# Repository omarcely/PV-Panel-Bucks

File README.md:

# PV-Panel-Bucks
Proyecto de electrónica de potencia

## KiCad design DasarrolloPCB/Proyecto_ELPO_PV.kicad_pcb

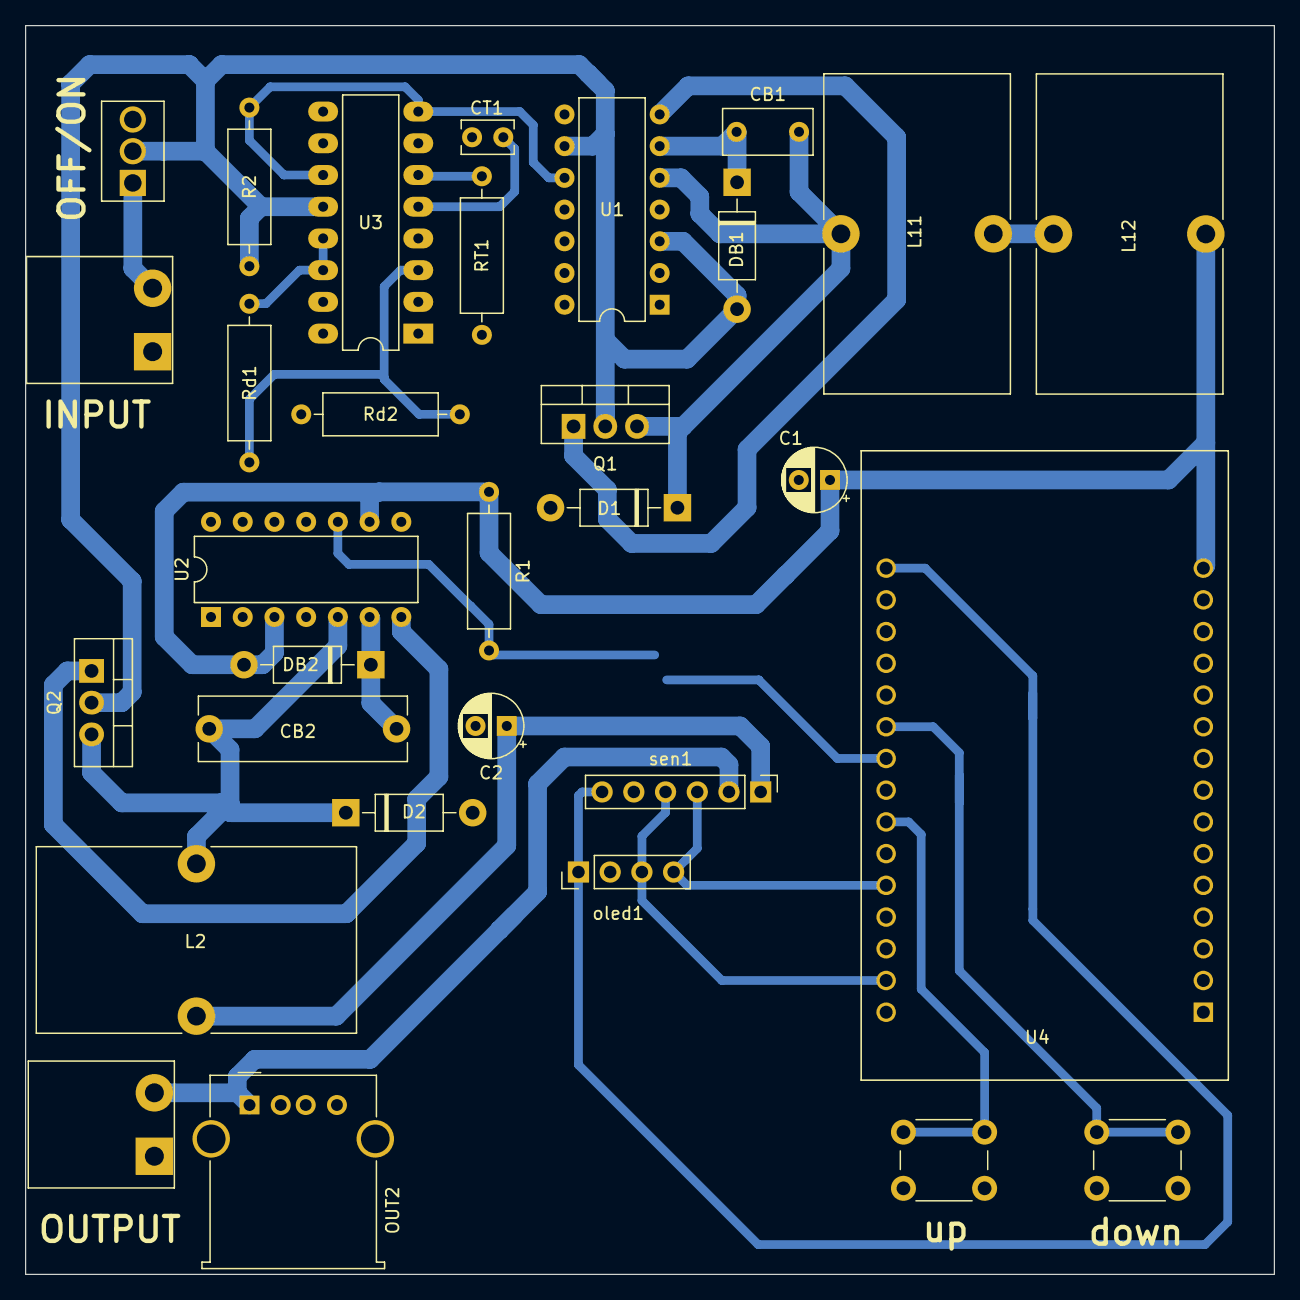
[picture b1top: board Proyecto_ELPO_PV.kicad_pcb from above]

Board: 2 copper layers, 100.0 x 100.0 mm, 32 parts (1 on the bottom side), 25 nets.

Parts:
C1: 10uf; CP_Radial_D5.0mm_P2.50mm
C2: 2.7uF; CP_Radial_D5.0mm_P2.50mm
CB1: 12n; C_Rect_L7.0mm_W3.5mm_P5.00mm
CB2: 0.47uF; C_Rect_L16.5mm_W5.0mm_P15.00mm_MKT
CT1: 5nF; C_Rect_L4.0mm_W2.5mm_P2.50mm
D1, D2: UF4005; D_DO-41_SOD81_P10.16mm_Horizontal
DB1, DB2: UF4005; D_DO-41_SOD81_P10.16mm_Horizontal
INPUT: Solar_Cell; TerminalBlock_bornier-2_P5.08mm
L2, L11, L12: 1mH; L_Toroid_Vertical_L25.4mm_W14.7mm_P12.20mm_Vishay_TJ5_BigPa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
OFF/ON: SW; PinHeader_1x02_P2.54mm_Horizontal
OUT2: USB_A; USB_A_Molex_67643_Horizontal
OUTPUT: bornera; TerminalBlock_bornier-2_P5.08mm
Q1, Q2: IRFZ44N; TO-220-3_Vertical
Q3: 2N7002; SOT-23
R1: 10k; R_Axial_DIN0309_L9.0mm_D3.2mm_P12.70mm_Horizontal
R2: 2.2k; R_Axial_DIN0309_L9.0mm_D3.2mm_P12.70mm_Horizontal
RT1: 2.2k; R_Axial_DIN0309_L9.0mm_D3.2mm_P12.70mm_Horizontal
Rd1: 150k; R_Axial_DIN0309_L9.0mm_D3.2mm_P12.70mm_Horizontal
Rd2: 120k; R_Axial_DIN0309_L9.0mm_D3.2mm_P12.70mm_Horizontal
U1, U2: IR2110; DIP-14_W7.62mm
U3: TL494; DIP-16_W7.62mm_LongPads
U4: ESP32-DEVKITC-32D; MODULE_ESP32-DEVKITC-32D
down: btn; SW_PUSH_6mm
oled1: 1.3'' 128x64; PinHeader_1x04_P2.54mm_Vertical
sen1: 1NA219; PinHeader_1x06_P2.54mm_Vertical
up: btn; SW_PUSH_6mm

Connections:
/TL494/PWM: R2.2, U1.10, U3.8, U3.11
/buck1/Vs: CB1.2, D1.1, L11.1, Q1.3, U1.5
/buck2/Vout: C2.1, L2.2, sen1.6
/buck2/Vs: CB2.2, D2.1, L2.1, Q2.3, U2.5
/driver1/PWM_out: Q1.1, U1.7
/driver2/PWM_in: Q3.3, R1.2, U2.10
/driver2/PWM_out: Q2.1, U2.7
/driver2/Vcc: C1.1, DB2.2, L12.2, R1.1, U2.3, U2.9, U4.1
GND: C1.2, C2.2, CT1.2, D1.2, D2.2, INPUT.2, OUT2.4, OUT2.5, OUTPUT.1, Q3.2, RT1.1, Rd2.1, U1.2, U1.11, U1.12, U1.13, U2.2, U2.11, U2.12, U2.13, U3.1, U3.2, U3.4, U3.7, U3.9, U3.10, U3.15, U3.16, U4.2, U4.29, down.2, oled1.3, sen1.2, up.2
unnamed: CB1.1, DB1.1, U1.6
unnamed: CB2.1, DB2.1, U2.6
unnamed: CT1.1, U3.5
unnamed: OUT2.1, OUTPUT.2, sen1.5
unnamed: L11.2, L12.1
unnamed: INPUT.1, OFF/ON.1
unnamed: Q3.1, U4.24
unnamed: RT1.2, U3.6
unnamed: Rd1.1, U3.13, U3.14
unnamed: Rd1.2, Rd2.2, U3.3
unnamed: U4.17, oled1.2, sen1.3
unnamed: U4.20, oled1.1, sen1.4
unnamed: U4.22, up.1
unnamed: U4.25, down.1
unnamed: U4.30, oled1.4, sen1.1
Vpv: DB1.2, OFF/ON.2, Q1.2, Q2.2, R2.1, U1.3, U1.9, U3.12

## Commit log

2022-02-05 PCB Terminada + archivos Gerber
2022-02-06 leyenda ON/OFF arreglada
